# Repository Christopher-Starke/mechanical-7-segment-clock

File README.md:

# mechanical-7-segment-clock
A large mechanical 7-segment clock using cheap stepper motors.  

##
Each digit requires its own controller board. The seconds digit acts as the master keeping time using the DS3231 RTC and sending I2C commands out to the other digits. The rest of the digits act as slaves receiving numbers via I2C and displaying the number. The minute tens digit needs I2C address #3 hours digit dress #2 and hours tens dress #1. 

## BOM
- 28x		28BYJ-48 5V stepper motors  
- 28x		ULN2003 darlington arrays
- 16x		7HCT 4094 8-bit shift registers 
- 28x		608 skateboard bearings
- 4x		Arduino nano 
- 4x		4 pole screw terminals 
- 1x 		Adafruit ds3231 RTC module
- 56x		M4x10 bolts (for anchoring stepper motors to the housing)
- 56x 		M4x25 bolts (for attaching the stepper casing to the backboard)

### Printed parts 
- 28x		Stepper housings 
- 28x		Levers

### Additional parts
- 1x		Backplate
- 28x		Digit faces

## Assembly
### Stepper motor housing assembly
Assembly of the stepper motor housing can be seen by clicking on the image below. 
Required parts 
- 1x		608 skateboard bearing (yellow)
- 1x		28BYJ-48 5V stepper motor
- 2x 		M4x10 bolts

Printed parts
- 1x 		Lever (red)
- 1x		Stepper Housing (blue)

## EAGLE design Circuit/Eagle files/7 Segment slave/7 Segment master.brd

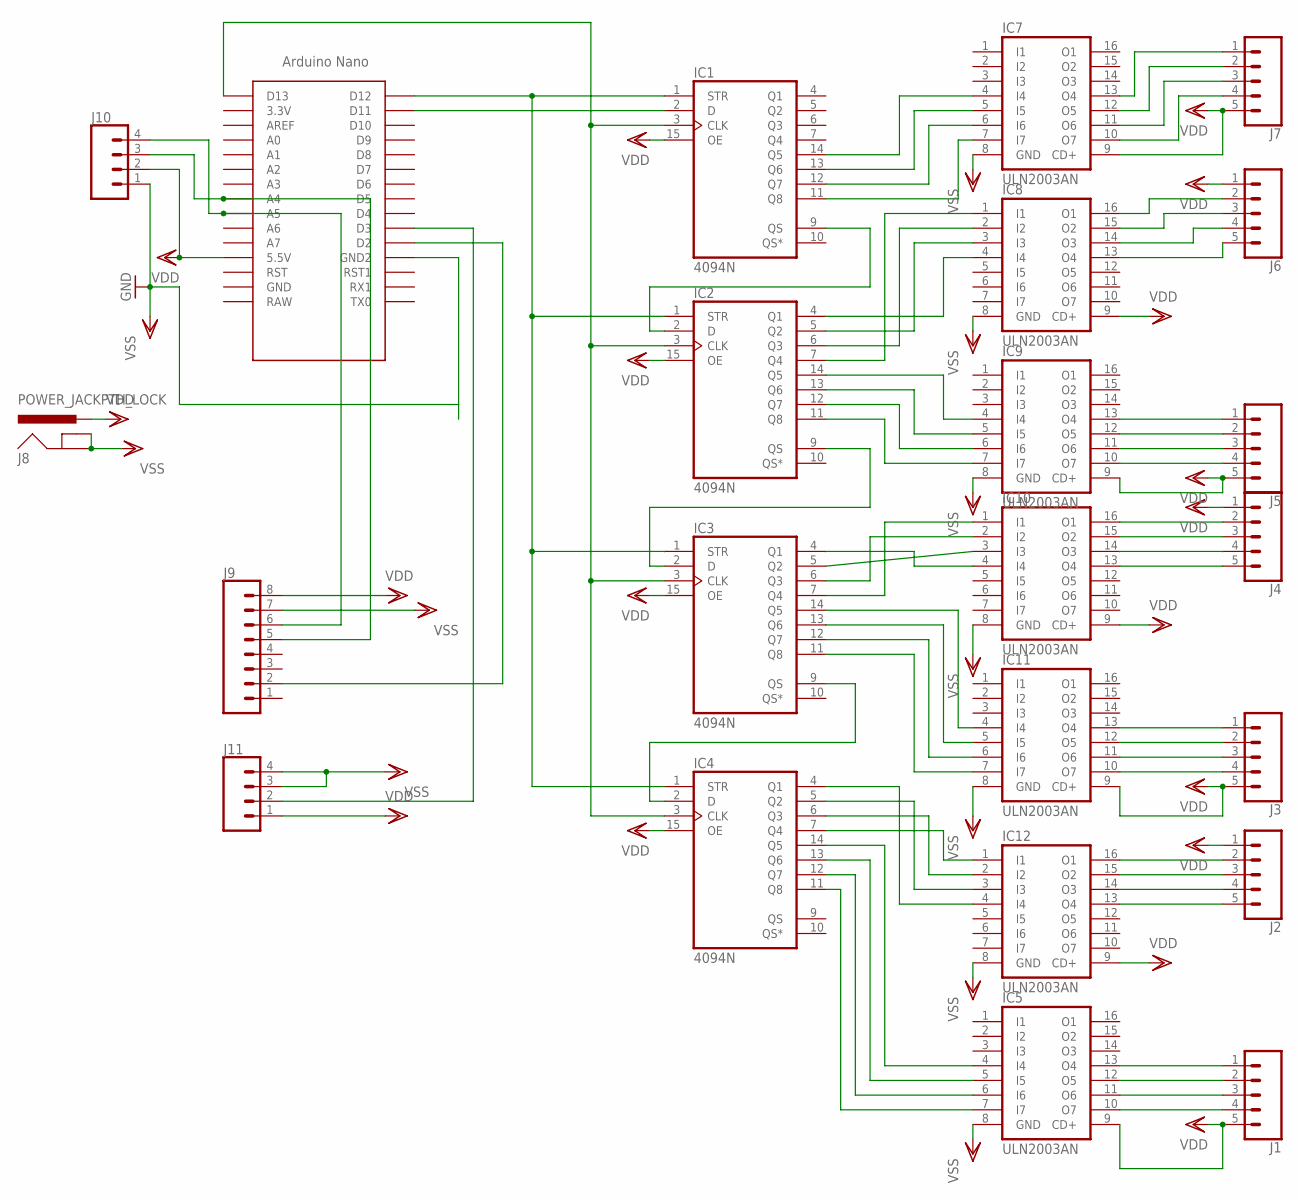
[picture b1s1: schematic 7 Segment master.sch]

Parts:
IC1, IC2, IC3, IC4: 4094N; DIL16
IC5, IC7, IC8, IC9, IC10, IC11, IC12: ULN2003AN; DIL16
J1, J2, J3, J4, J5, J6, J7: CONN_05LOCK_LONGPADS; 1X05_LOCK_LONGPADS
J8: POWER_JACKPTH_LOCK; POWER_JACK_PTH_LOCK
J9: CONN_08LOCK_LONGPADS; 1X08_LOCK_LONGPADS
J10: CONN_04; SCREWTERMINAL-5MM-4
J11: CONN_04LOCK_LONGPADS; 1X04_LOCK_LONGPADS
U$1: NANO

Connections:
unnamed: IC1.3 (CLK), IC2.3 (CLK), IC3.3 (CLK), IC4.3 (CLK), U$1.D13
unnamed: IC1.2 (D), U$1.D11
unnamed: IC1.9 (QS), IC2.2 (D)
unnamed: IC2.9 (QS), IC3.2 (D)
unnamed: IC1.1 (STR), IC2.1 (STR), IC3.1 (STR), IC4.1 (STR), U$1.D12
unnamed: IC3.9 (QS), IC4.2 (D)
unnamed: IC1.14 (Q5), IC7.4 (I4)
unnamed: IC1.13 (Q6), IC7.5 (I5)
unnamed: IC1.12 (Q7), IC7.6 (I6)
unnamed: IC1.11 (Q8), IC7.7 (I7)
unnamed: IC2.4 (Q1), IC8.4 (I4)
unnamed: IC2.5 (Q2), IC8.3 (I3)
unnamed: IC2.6 (Q3), IC8.2 (I2)
unnamed: IC2.7 (Q4), IC8.1 (I1)
unnamed: IC2.14 (Q5), IC9.4 (I4)
unnamed: IC2.11 (Q8), IC9.7 (I7)
unnamed: IC2.12 (Q7), IC9.6 (I6)
unnamed: IC2.13 (Q6), IC9.5 (I5)
unnamed: IC3.4 (Q1), IC10.4 (I4)
unnamed: IC3.5 (Q2), IC10.3 (I3)
unnamed: IC3.6 (Q3), IC10.2 (I2)
unnamed: IC3.7 (Q4), IC10.1 (I1)
unnamed: IC3.14 (Q5), IC11.4 (I4)
unnamed: IC3.13 (Q6), IC11.5 (I5)
unnamed: IC3.12 (Q7), IC11.6 (I6)
unnamed: IC3.11 (Q8), IC11.7 (I7)
unnamed: IC4.4 (Q1), IC12.4 (I4)
unnamed: IC4.5 (Q2), IC12.3 (I3)
unnamed: IC4.6 (Q3), IC12.2 (I2)
unnamed: IC4.7 (Q4), IC12.1 (I1)
unnamed: IC4.14 (Q5), IC5.4 (I4)
unnamed: IC4.13 (Q6), IC5.5 (I5)
unnamed: IC4.12 (Q7), IC5.6 (I6)
unnamed: IC4.11 (Q8), IC5.7 (I7)
unnamed: IC7.10 (O7), J7.4
unnamed: IC7.11 (O6), J7.3
unnamed: IC7.12 (O5), J7.2
unnamed: IC7.13 (O4), J7.1
unnamed: IC8.16 (O1), J6.2
unnamed: IC8.15 (O2), J6.3
unnamed: IC8.14 (O3), J6.4
unnamed: IC8.13 (O4), J6.5
unnamed: IC9.13 (O4), J5.1
unnamed: IC9.12 (O5), J5.2
unnamed: IC9.11 (O6), J5.3
unnamed: IC9.10 (O7), J5.4
unnamed: IC10.16 (O1), J4.2
unnamed: IC10.15 (O2), J4.3
unnamed: IC10.14 (O3), J4.4
unnamed: IC10.13 (O4), J4.5
unnamed: IC11.13 (O4), J3.1
unnamed: IC11.12 (O5), J3.2
unnamed: IC11.11 (O6), J3.3
unnamed: IC11.10 (O7), J3.4
unnamed: IC12.16 (O1), J2.2
unnamed: IC12.15 (O2), J2.3
unnamed: IC12.14 (O3), J2.4
unnamed: IC12.13 (O4), J2.5
unnamed: IC5.13 (O4), J1.1
unnamed: IC5.12 (O5), J1.2
unnamed: IC5.11 (O6), J1.3
unnamed: IC5.10 (O7), J1.4
unnamed: J9.6, J10.4, U$1.A5
unnamed: J9.5, J10.3, U$1.A4
unnamed: J9.2, U$1.D2
unnamed: J11.2, U$1.D3
VDD: IC1.15 (OE), IC1.16 (VDD), IC2.15 (OE), IC2.16 (VDD), IC3.15 (OE), IC3.16 (VDD), IC4.15 (OE), IC4.16 (VDD), IC5.9 (CD+), IC7.9 (CD+), IC8.9 (CD+), IC9.9 (CD+), IC10.9 (CD+), IC11.9 (CD+), IC12.9 (CD+), J1.5, J2.1, J3.5, J4.1, J5.5, J6.1, J7.5, J8.PWR, J9.8, J10.2, J11.1, U$1.5V (5.5V)
VSS: IC1.8 (VSS), IC2.8 (VSS), IC3.8 (VSS), IC4.8 (VSS), IC5.8 (GND), IC7.8 (GND), IC8.8 (GND), IC9.8 (GND), IC10.8 (GND), IC11.8 (GND), IC12.8 (GND), J8.GND, J8.GNDBREAK, J9.7, J10.1, J11.3, J11.4, U$1.GND1 (GND2)

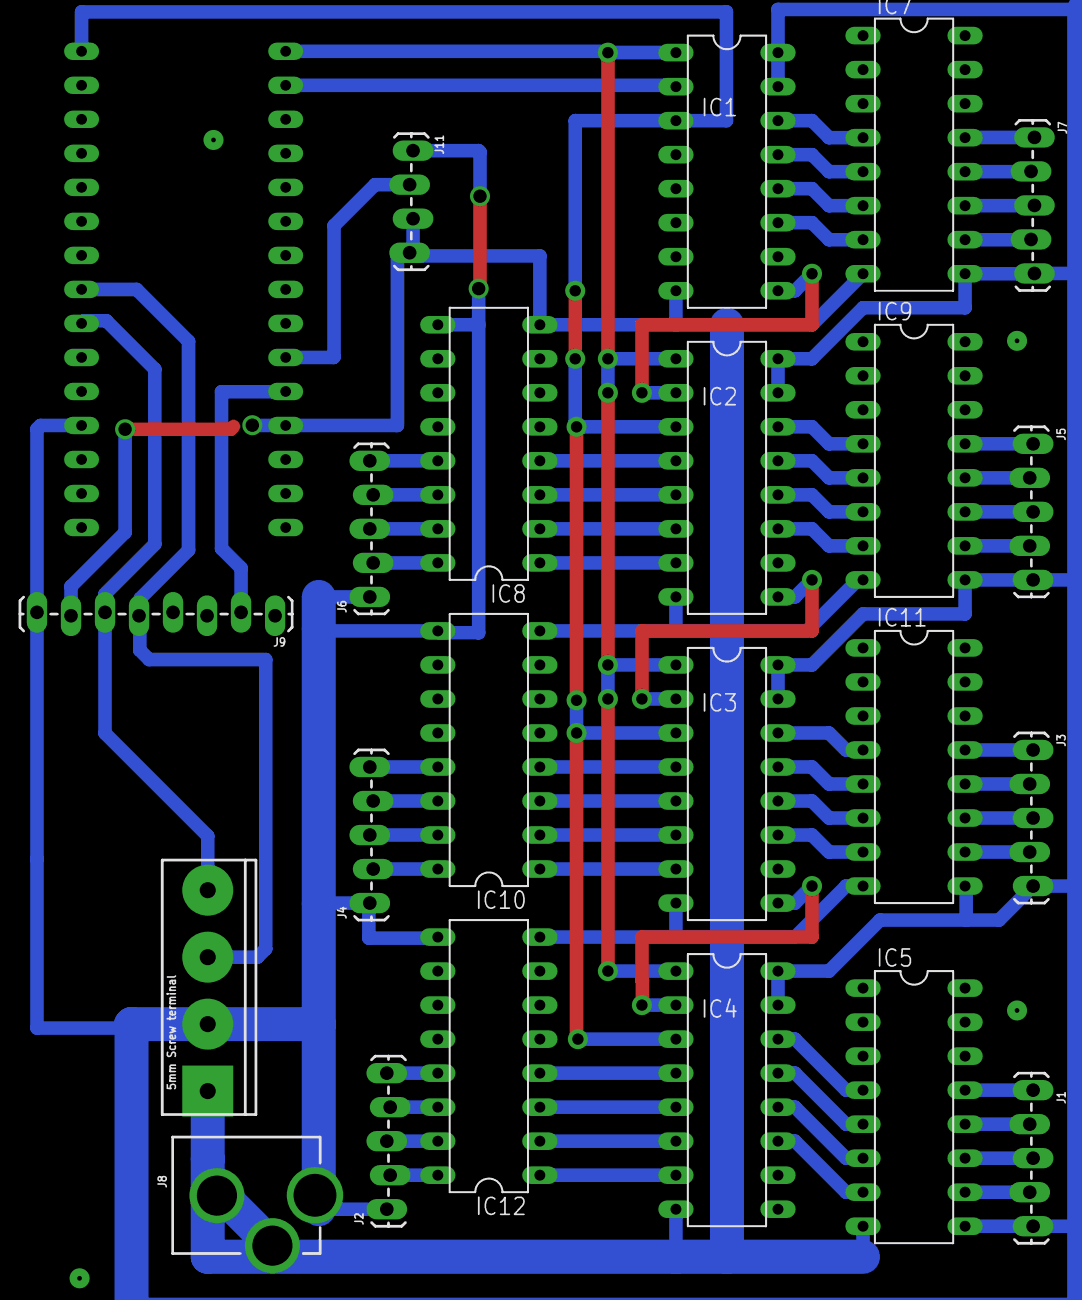
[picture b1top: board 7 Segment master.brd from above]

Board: 2 copper layers, 23 parts (0 on the bottom side), 68 nets.

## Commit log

2021-09-07 main push
2021-09-07 Readme update
2021-09-11 Added link to asembley video
2021-09-11 Fixed bad link
2021-09-11 Added steps
2021-09-12 Circuit

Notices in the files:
parts and their libraries:
SparkFun-Connectors: Licensing: Creative Commons ShareAlike 4.0 International - https://creativecommons.org/licenses/by-sa/4.0
